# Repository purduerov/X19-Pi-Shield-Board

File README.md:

# Purdue ROV KiCad Board Template

Starter template for new PCB designs in Purdue ROV. Pre-configured with the team component library submodule, automatic Git clean filters, isolation rules, and CI/CD validation.

---

## 🚀 Quickstart: Opening the Project (Recommended)

**Always open the project using the 1-click launcher:**

* **Windows:** Double-click `LAUNCH_KICAD.bat`
* **macOS / Linux:** Run `./LAUNCH_KICAD.sh`

### What the Launcher Does Automatically:
1. ⚙️ **Configures Git Hooks & Clean Filters:** Sets up Git to strip volatile viewport/zoom coordinates on every commit, preventing merge conflicts.
2. 🔄 **Auto-Updates Component Library:** Pulls the freshest symbols, footprints, and 3D models from `purdue-rov-kicad-lib` before opening.
3. 📐 **Opens KiCad:** Launches the project file with all 6 central library categories pre-linked.

---

## Creating a New Board Repository

1. In GitHub, click **Use this template** > **Create a new repository**.
2. Name the repo to match the board function (e.g. `thruster-interface-board`).
3. Clone recursively so submodules are pulled:
   ```bash
   git clone --recursive https://github.com/purduerov/<your-repo-name>.git
   cd <your-repo-name>
   ```
   If cloned without `--recursive`, initialize the submodule:
   ```bash
   git submodule update --init --recursive
   ```

4. Prepare the board with `bootstrap.py` (renames starter files, writes the manifest, and installs the validation hook; `LAUNCH_KICAD` runs this automatically):
   ```bash
   python bootstrap.py --project-dir . --non-interactive
   ```

## Central Component Library & Manager GUI

The template is pre-configured with project-level library tables (`sym-lib-table` and `fp-lib-table`) pointing to `purdue-rov-kicad-lib`:
- `rov_passives`: Resistors, capacitors, inductors, crystals
- `rov_power`: Voltage regulators, buck/boost converters, MOSFETs, diodes
- `rov_logic`: MCUs, logic ICs, op-amps, level shifters, transceivers
- `rov_connectors`: Power terminals, XT60/XT30, headers, USB, JST connectors
- `rov_sensors`: IMUs, temperature, pressure sensors
- `rov_mech`: Mounting holes, standoffs, test points

### Launching the Library Manager GUI
To browse parts, inspect footprints, edit properties, or add/delete components in the shared library:
- **Windows:** Double-click `libs\purdue-rov-kicad-lib\LIBRARY_MANAGER.bat`
- **macOS / Linux:** Run `./libs/purdue-rov-kicad-lib/LIBRARY_MANAGER.sh`

## Design Rules & Clearances

- Clearance rules (JLCPCB 4-layer rules) are defined in `X19-Pi-Shield-Board.kicad_dru`.
- High-power thruster nets require a minimum 2.0 mm clearance from low-voltage logic (3.3V / 5V).

## Automated CI/CD & DevOps Preflight Checks

All CI/CD automation and tooling are centralized in [`purduerov/pcb-devops`](https://github.com/purduerov/pcb-devops):
1. **Automated Git Clean Filters:** Configured automatically by `.githooks/pre-commit` to prevent viewport/zoom merge noise.
2. **KiCad Symbol Linting:** Validates mandatory fields (`MPN`, `Manufacturer`, `Category`, `DigiKey`, `Datasheet`, `Temp_Range`) on all library components.
3. **ERC & DRC Validation:** Executes Electrical and Design Rules Checks via KiBot in GitHub Actions.
4. **Artifact Generation:** Automatically exports Schematic PDFs, Board Layout PDFs, and Interactive HTML BOMs on every pull request.

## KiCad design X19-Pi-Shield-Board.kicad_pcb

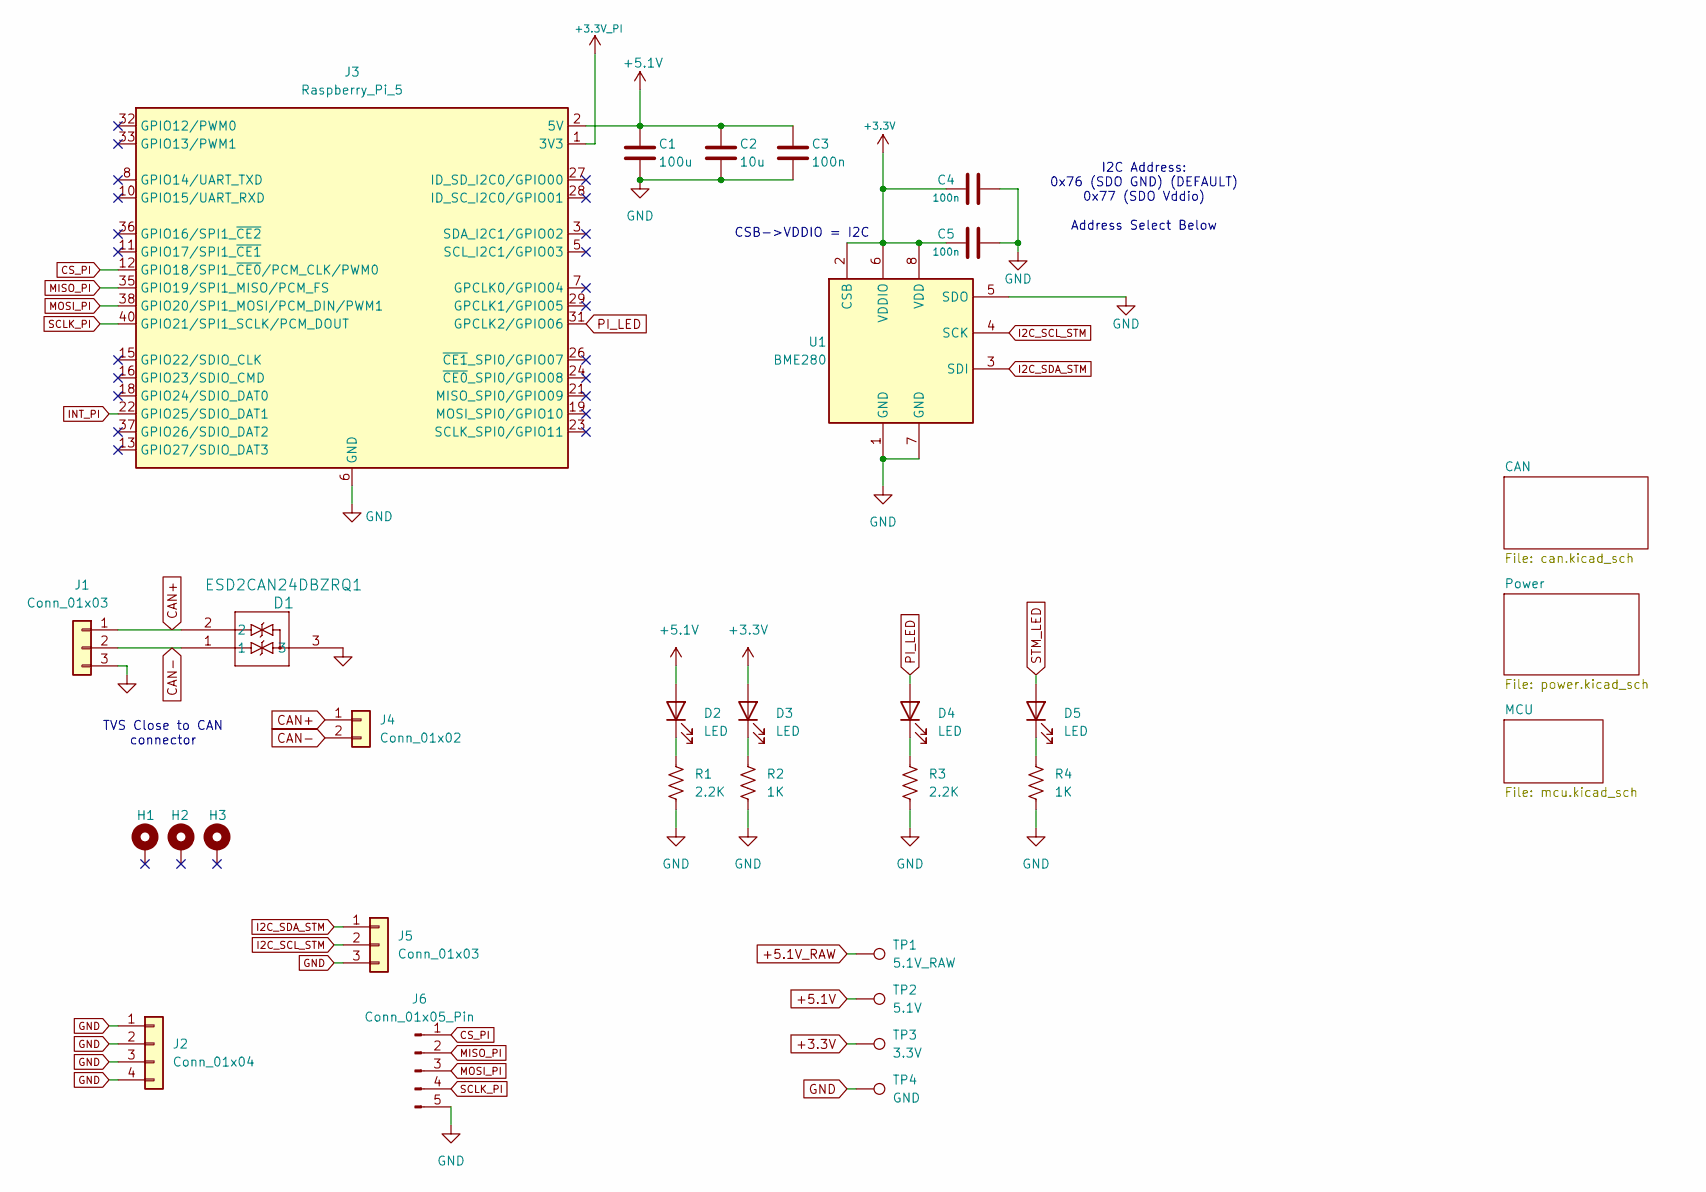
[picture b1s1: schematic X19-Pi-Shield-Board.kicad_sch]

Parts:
C1: 100u; CP_Elec_6.3x5.4; Part Number 865080343009
C2: 10u; C_0603_1608Metric_Pad1.08x0.95mm_HandSolder; Part Number CC0603MRX5R6BB106
C3, C4, C5: 100n; C_0603_1608Metric_Pad1.08x0.95mm_HandSolder; Part Number CC0603KRX7R8BB104
D1: ESD2CAN24DBZRQ1; SOT-23-3; Part Number ESD2CAN24DBZRQ1
D2, D3, D4, D5: LED; LED_0603_1608Metric_Pad1.05x0.95mm_HandSolder; Part Number LTST-C190GKT
H1, H2, H3: MountingHole_Pad; MountingHole_2.7mm_M2.5_Pad
J1: Conn_01x03; Molex_Micro-Fit_3.0_43650-0300_1x03_P3.00mm_Horizontal; Part Number 43650-0300
J2: Conn_01x04; PinHeader_1x04_P2.54mm_Vertical; Part Number Generic 2.54mm Pinheader
J3: Raspberry_Pi_5; PinSocket_2x20_P2.54mm_Vertical; Part Number 1528-1385-ND
J4: Conn_01x02; PinHeader_1x02_P2.54mm_Vertical; Part Number Generic 2.54mm Pinheader
J5: Conn_01x03; PinHeader_1x03_P2.54mm_Vertical; Part Number Generic 2.54mm Pinheader
J6: Conn_01x05_Pin; PinHeader_1x05_P2.54mm_Vertical; Part Number Generic 2.54mm Pinheader
R1, R3: 2.2K; R_0603_1608Metric_Pad0.98x0.95mm_HandSolder; Part Number RC0603FR-072K2L
R2, R4: 1K; R_0603_1608Metric_Pad0.98x0.95mm_HandSolder; Part Number RC0603FR-071KL
TP1: 5.1V_RAW; TestPoint_Pad_D1.0mm
TP2: 5.1V; TestPoint_Pad_D1.0mm
TP3: 3.3V; TestPoint_Pad_D1.0mm
TP4: GND; TestPoint_Pad_D1.0mm
U1: BME280; Bosch_LGA-8_2.5x2.5mm_P0.65mm_ClockwisePinNumbering; Part Number BME280

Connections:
+3.3V: C4.2, C5.1, D3.2 (A), TP3.1 (1_1), U1.2 (CSB), U1.6 (VDDIO), U1.8 (VDD); also elsewhere on the board
+3.3V_PI: J3.1 (3V3), J3.17 (3V3); also elsewhere on the board
+5.1V: C1.1, C2.1, C3.1, D2.2 (A), J3.2 (5V), J3.4 (5V), TP2.1 (1_1); also elsewhere on the board
+5.1V_RAW: TP1.1 (1_1); also elsewhere on the board
CAN+: D1.2, J1.1, J4.1; also elsewhere on the board
CAN-: D1.1, J1.2, J4.2; also elsewhere on the board
CS_PI: J3.12 (GPIO18/SPI1_~CE0/PCM_CLK/PWM0), J6.1; also elsewhere on the board
GND: C1.2, C2.2, C3.2, C4.1, C5.2, D1.3, J1.3, J2.1, J2.2, J2.3, J2.4, J3.6 (GND), J3.9 (GND), J3.14 (GND), J3.20 (GND), J3.25 (GND), J3.30 (GND), J3.34 (GND), J3.39 (GND), J5.3, J6.5, R1.2, R2.2, R3.2, R4.2, TP4.1 (1_1), U1.1 (GND), U1.5 (SDO), U1.7 (GND); also elsewhere on the board
I2C_SCL_STM: J5.2, U1.4 (SCK); also elsewhere on the board
I2C_SDA_STM: J5.1, U1.3 (SDI); also elsewhere on the board
INT_PI: J3.22 (GPIO25/SDIO_DAT1); also elsewhere on the board
MISO_PI: J3.35 (GPIO19/SPI1_MISO/PCM_FS), J6.2; also elsewhere on the board
MOSI_PI: J3.38 (GPIO20/SPI1_MOSI/PCM_DIN/PWM1), J6.3; also elsewhere on the board
unnamed: D2.1 (K), R1.1
unnamed: D3.1 (K), R2.1
unnamed: D4.1 (K), R3.1
unnamed: D5.1 (K), R4.1
PI_LED: D4.2 (A), J3.31 (GPCLK2/GPIO06)
SCLK_PI: J3.40 (GPIO21/SPI1_SCLK/PCM_DOUT), J6.4; also elsewhere on the board
STM_LED: D5.2 (A); also elsewhere on the board

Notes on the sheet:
CSB->VDDIO = I2C
TVS Close to CAN connector
I2C Address: 0x76 (SDO GND) (DEFAULT) 0x77 (SDO Vddio) Address Select Below

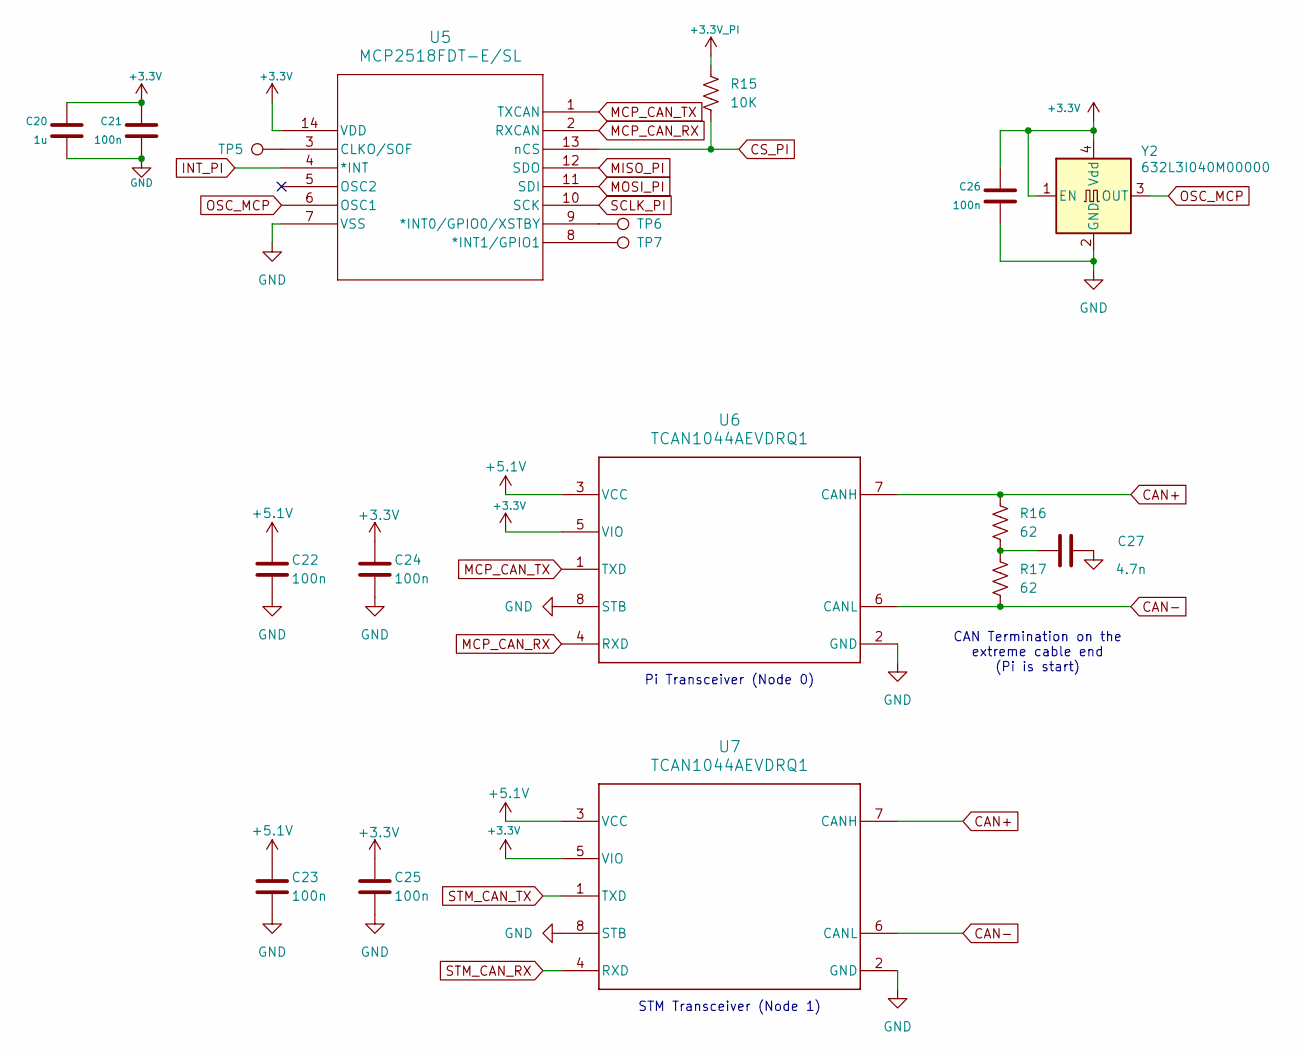
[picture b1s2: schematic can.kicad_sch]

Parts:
C20: 1u; C_0603_1608Metric_Pad1.08x0.95mm_HandSolder; Part Number CC0603KRX5R6BB105
C21, C22, C23, C24, C25, C26: 100n; C_0603_1608Metric_Pad1.08x0.95mm_HandSolder; Part Number CC0603KRX7R8BB104
C27: 4.7n; C_0603_1608Metric_Pad1.08x0.95mm_HandSolder; Part Number CC0603KRX7R9BB472
R15: 10K; R_0603_1608Metric_Pad0.98x0.95mm_HandSolder; Part Number RC0603FR-0710KL
R16, R17: 62; R_0603_1608Metric_Pad0.98x0.95mm_HandSolder; Part Number RC0603FR-0762RL
TP5: SOF1; TestPoint_Pad_D1.0mm
TP6: INT0; TestPoint_Pad_D1.0mm
TP7: INT1; TestPoint_Pad_D1.0mm
U5: MCP2518FDT-E/SL; SOIC-14_3.9x8.7mm_P1.27mm; Part Number MCP2518FDT-E/SL
U6, U7: TCAN1044AEVDRQ1; SOIC-8_3.9x4.9mm_P1.27mm; Part Number TCAN1044AEVDRQ1
Y2: 632L3I040M00000; Crystal_SMD_3225-4Pin_3.2x2.5mm; Part Number 632L3I040M00000

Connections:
+3.3V: C20.1, C21.1, C24.1, C25.1, C26.1, U5.14 (VDD), U6.5 (VIO), U7.5 (VIO), Y2.1 (EN), Y2.4 (Vdd); also elsewhere on the board
+3.3V_PI: R15.1; also elsewhere on the board
+5.1V: C22.1, C23.1, U6.3 (VCC), U7.3 (VCC); also elsewhere on the board
CAN+: R16.1, U6.7 (CANH), U7.7 (CANH); also elsewhere on the board
CAN-: R17.2, U6.6 (CANL), U7.6 (CANL); also elsewhere on the board
CS_PI: R15.2, U5.13 (nCS); also elsewhere on the board
GND: C20.2, C21.2, C22.2, C23.2, C24.2, C25.2, C26.2, C27.2, U5.7 (VSS), U6.2 (GND), U6.8 (STB), U7.2 (GND), U7.8 (STB), Y2.2 (GND); also elsewhere on the board
INT_PI: U5.4 (*INT); also elsewhere on the board
MCP_CAN_RX: U5.2 (RXCAN), U6.4 (RXD)
MCP_CAN_TX: U5.1 (TXCAN), U6.1 (TXD)
MISO_PI: U5.12 (SDO); also elsewhere on the board
MOSI_PI: U5.11 (SDI); also elsewhere on the board
unnamed: C27.1, R16.2, R17.1
unnamed: TP6.1 (1_1), U5.9 (*INT0/GPIO0/XSTBY)
unnamed: TP7.1 (1_1), U5.8 (*INT1/GPIO1)
unnamed: TP5.1 (1_1), U5.3 (CLKO/SOF)
OSC_MCP: U5.6 (OSC1), Y2.3 (OUT)
SCLK_PI: U5.10 (SCK); also elsewhere on the board
STM_CAN_RX: U7.4 (RXD); also elsewhere on the board
STM_CAN_TX: U7.1 (TXD); also elsewhere on the board

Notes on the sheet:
CAN Termination on the extreme cable end (Pi is start)
Pi Transceiver (Node 0)
STM Transceiver (Node 1)

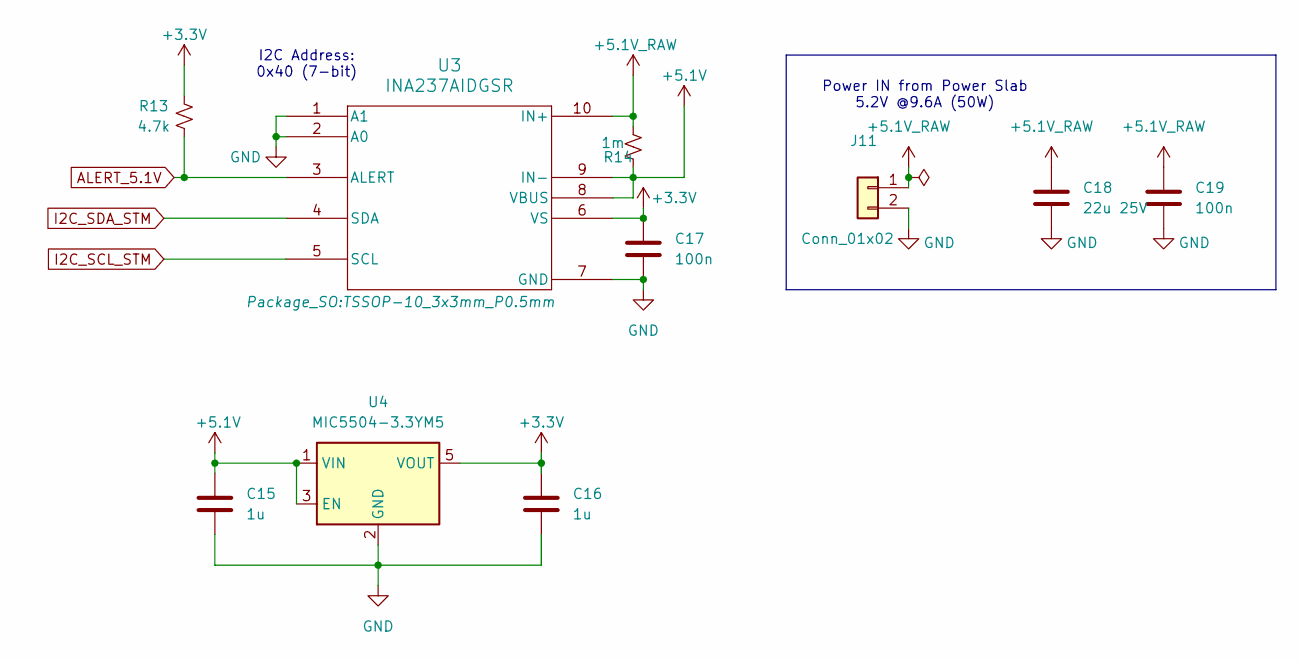
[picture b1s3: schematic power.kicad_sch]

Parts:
C15, C16: 1u; C_0603_1608Metric_Pad1.08x0.95mm_HandSolder; Part Number CC0603KRX5R6BB105
C17, C19: 100n; C_0603_1608Metric_Pad1.08x0.95mm_HandSolder; Part Number CC0603KRX7R8BB104
C18: 22u 25V; C_1206_3216Metric_Pad1.33x1.80mm_HandSolder; Part Number CC1206KKX5R8BB226
J11: Conn_01x02; Molex_Micro-Fit_3.0_43650-0200_1x02_P3.00mm_Horizontal; Part Number 43650-0200
R13: 4.7k; R_0603_1608Metric_Pad0.98x0.95mm_HandSolder; Part Number RC0603FR-074K7L
R14: 1m; R_1206_3216Metric_Pad1.30x1.75mm_HandSolder; Part Number PCS1206FR0010ET
U3: INA237AIDGSR; TSSOP-10_3x3mm_P0.5mm; Part Number INA237AIDGSR
U4: MIC5504-3.3YM5; SOT-23-5; Part Number MIC5504-3.3YM5-TR

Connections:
+3.3V: C16.1, C17.1, R13.2, U3.6 (VS), U4.5 (VOUT); also elsewhere on the board
+5.1V: C15.1, R14.1, U3.8 (VBUS), U3.9 (IN-), U4.1 (VIN), U4.3 (EN); also elsewhere on the board
+5.1V_RAW: C18.1, C19.1, J11.1, R14.2, U3.10 (IN+); also elsewhere on the board
ALERT_5.1V: R13.1, U3.3 (ALERT); also elsewhere on the board
GND: C15.2, C16.2, C17.2, C18.2, C19.2, J11.2, U3.1 (A1), U3.2 (A0), U3.7 (GND), U4.2 (GND); also elsewhere on the board
I2C_SCL_STM: U3.5 (SCL); also elsewhere on the board
I2C_SDA_STM: U3.4 (SDA); also elsewhere on the board

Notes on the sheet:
I2C Address: 0x40 (7-bit)
Power IN from Power Slab 5.2V @9.6A (50W)

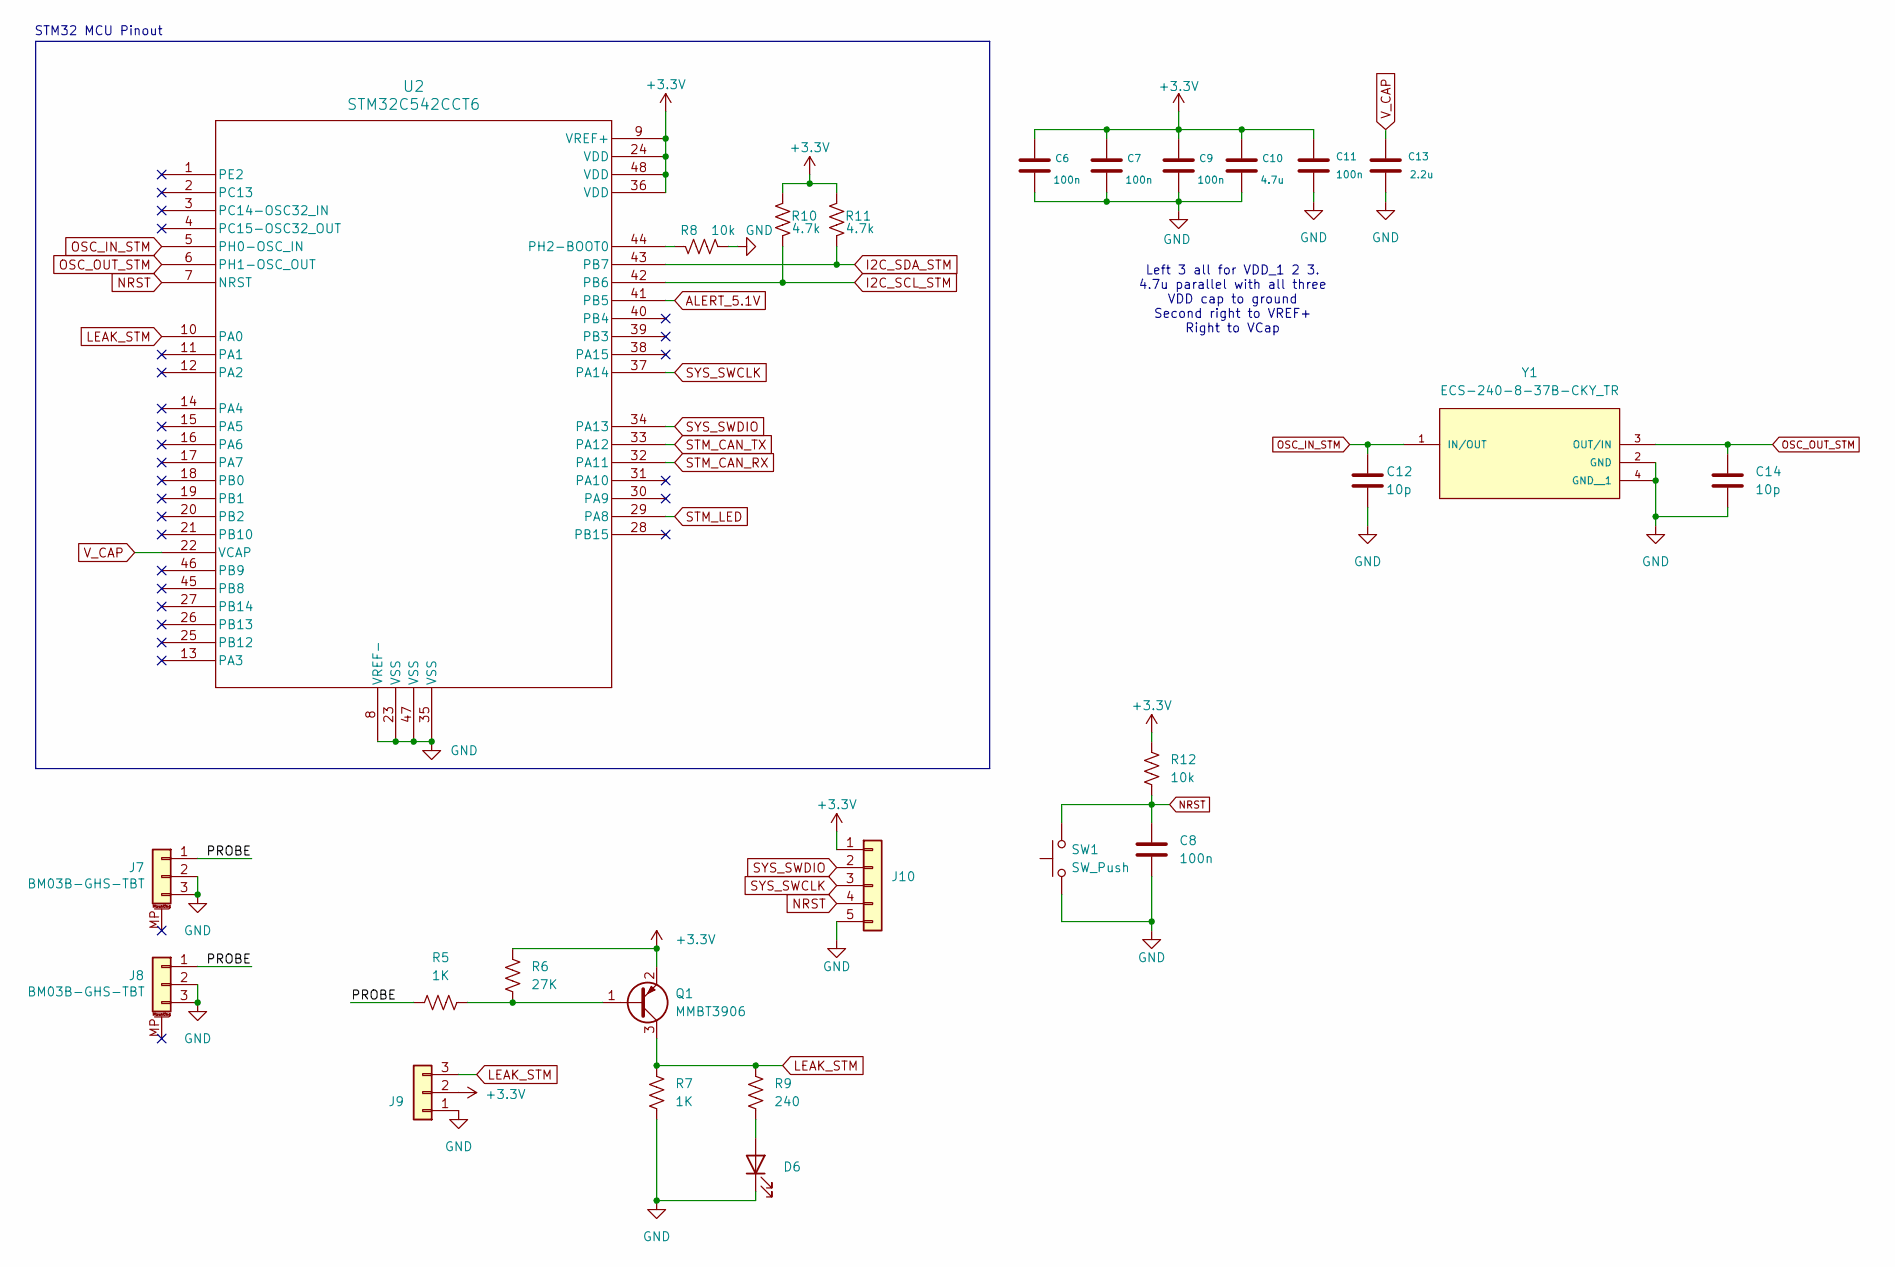
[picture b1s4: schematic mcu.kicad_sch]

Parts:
C6, C7, C8, C9, C11: 100n; C_0603_1608Metric_Pad1.08x0.95mm_HandSolder; Part Number CC0603KRX7R8BB104
C10: 4.7u; C_0603_1608Metric_Pad1.08x0.95mm_HandSolder; Part Number CC0603KRX5R6BB475
C12, C14: 10p; C_0603_1608Metric_Pad1.08x0.95mm_HandSolder; Part Number CC0603JRNPO9BN100
C13: 2.2u; C_0603_1608Metric_Pad1.08x0.95mm_HandSolder; Part Number CC0603KRX5R6BB225
D6: LED; LED_0603_1608Metric_Pad1.05x0.95mm_HandSolder; Part Number LTST-C190GKT
J7, J8: BM03B-GHS-TBT; JST_GH_BM03B-GHS-TBT_1x03-1MP_P1.25mm_Vertical; Part Number BM03B-GHS-TBT
J9: Conn_01x03; PinHeader_1x03_P2.54mm_Vertical; Part Number Generic 2.54mm Pinheader
J10: Conn_01x05; PinHeader_1x05_P2.54mm_Vertical; Part Number Generic 2.54mm Pinheader
Q1: MMBT3906; SOT-23; Part Number MMBT3906
R5, R7: 1K; R_0603_1608Metric_Pad0.98x0.95mm_HandSolder; Part Number RC0603FR-071KL
R6: 27K; R_0603_1608Metric_Pad0.98x0.95mm_HandSolder; Part Number RC0603FR-0727KL
R8, R12: 10k; R_0603_1608Metric_Pad0.98x0.95mm_HandSolder; Part Number RC0603FR-0710KL
R9: 240; R_0603_1608Metric_Pad0.98x0.95mm_HandSolder; Part Number RC0603FR-07240RL
R10, R11: 4.7k; R_0603_1608Metric_Pad0.98x0.95mm_HandSolder; Part Number RC0603FR-074K7L
SW1: SW_Push; SW_SPST_B3U-1000P; Part Number B3U-1000P
U2: STM32C542CCT6; LQFP-48_7x7mm_P0.5mm; Part Number STM32C542CCT6
Y1: ECS-240-8-37B-CKY_TR; Crystal_SMD_2016-4Pin_2.0x1.6mm; Part Number ECS-240-8-37B-CKY-TR

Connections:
+3.3V: C6.1, C7.1, C9.1, C10.1, C11.1, J9.2, J10.1, Q1.2 (E), R6.1, R10.2, R11.2, R12.1, U2.9 (VREF+), U2.24 (VDD), U2.36 (VDD), U2.48 (VDD); also elsewhere on the board
/MCU/PROBE: J7.1, J8.1, R5.1
ALERT_5.1V: U2.41 (PB5); also elsewhere on the board
GND: C6.2, C7.2, C8.2, C9.2, C10.2, C11.2, C12.1, C13.2, C14.2, D6.1 (K), J7.2, J7.3, J8.2, J8.3, J9.1, J10.5, R7.2, R8.1, SW1.1, U2.8 (VREF-), U2.23 (VSS), U2.35 (VSS), U2.47 (VSS), Y1.2 (GND), Y1.4 (GND__1); also elsewhere on the board
I2C_SCL_STM: R10.1, U2.42 (PB6); also elsewhere on the board
I2C_SDA_STM: R11.1, U2.43 (PB7); also elsewhere on the board
LEAK_STM: J9.3, Q1.3 (C), R7.1, R9.1, U2.10 (PA0)
NRST: C8.1, J10.4, R12.2, SW1.2, U2.7 (NRST)
unnamed: D6.2 (A), R9.2
unnamed: Q1.1 (B), R5.2, R6.2
unnamed: R8.2, U2.44 (PH2-BOOT0)
OSC_IN_STM: C12.2, U2.5 (PH0-OSC_IN), Y1.1 (IN/OUT)
OSC_OUT_STM: C14.1, U2.6 (PH1-OSC_OUT), Y1.3 (OUT/IN)
STM_CAN_RX: U2.32 (PA11); also elsewhere on the board
STM_CAN_TX: U2.33 (PA12); also elsewhere on the board
STM_LED: U2.29 (PA8); also elsewhere on the board
SYS_SWCLK: J10.3, U2.37 (PA14)
SYS_SWDIO: J10.2, U2.34 (PA13)
V_CAP: C13.1, U2.22 (VCAP)

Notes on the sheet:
STM32 MCU Pinout
Left 3 all for VDD_1 2 3. 4.7u parallel with all three VDD cap to ground Second right to VREF+ Right to VCap

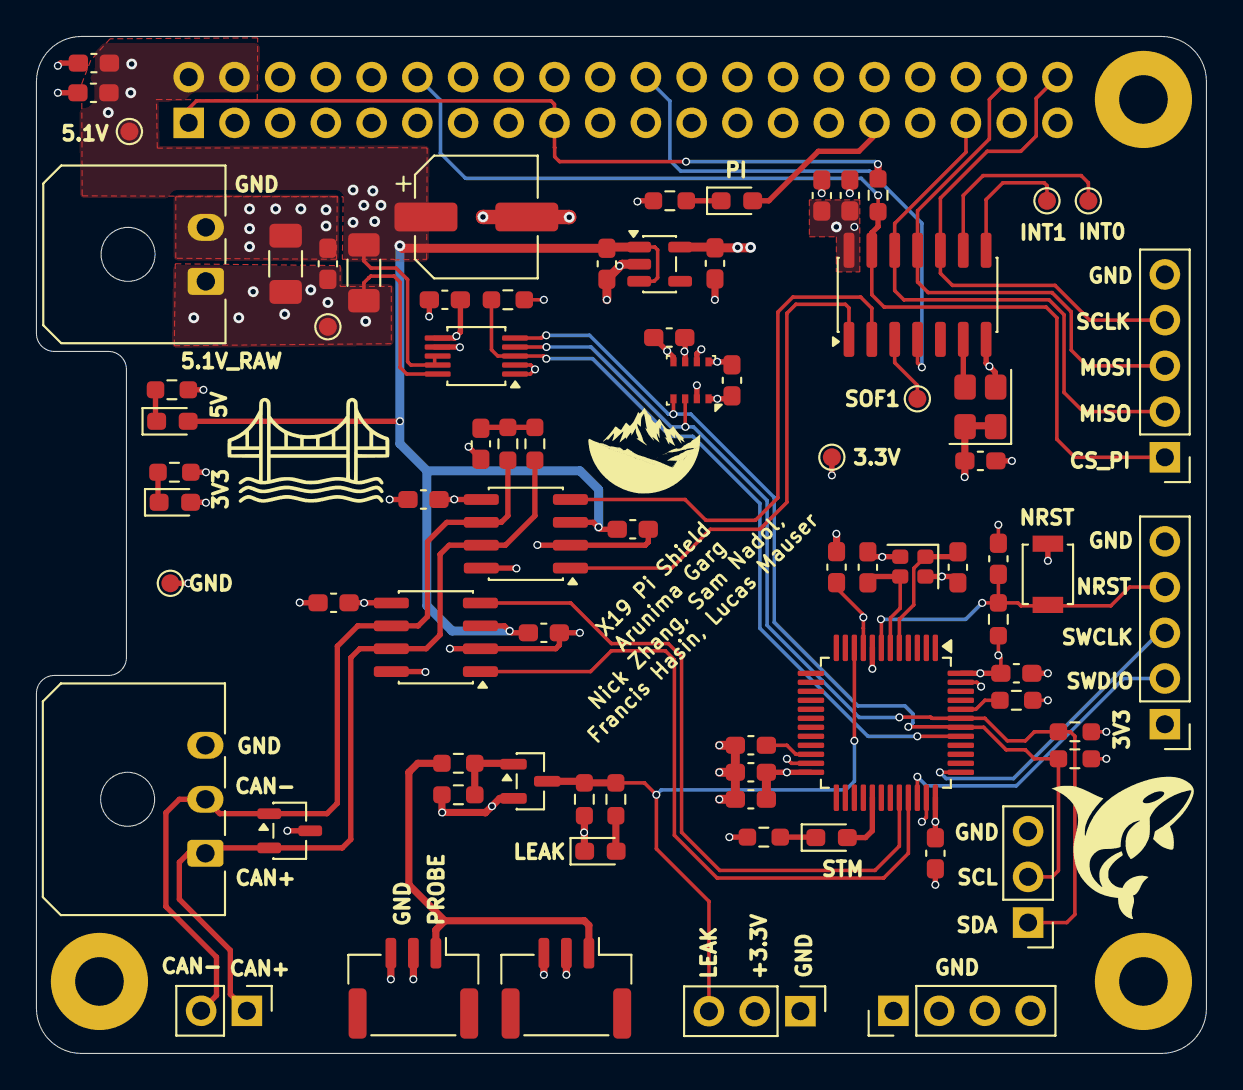
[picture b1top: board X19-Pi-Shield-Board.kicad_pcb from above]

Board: 4 copper layers, 65.0 x 56.5 mm, 82 parts (1 on the bottom side), 41 nets.

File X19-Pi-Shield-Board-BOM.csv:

Row,Description,Part,References,Value,Footprint,Quantity Per PCB,Status,Datasheet,digikey,Part Number,Sim.Pins,MF,PACKAGE,PRICE,STANDARD,MP,AVAILABILITY,Sim.Device
1,Unpolarized capacitor,C,C12 C14,10p,C_0603_1608Metric_Pad1.08x0.95mm_HandSolder,2, ,,,CC0603JRNPO9BN100,,,,,,,,
2,Unpolarized capacitor,C,C27,4.7n,C_0603_1608Metric_Pad1.08x0.95mm_HandSolder,1, ,,,CC0603KRX7R9BB472,,,,,,,,
3,Unpolarized capacitor,C,C3 C4 C5 C6 C7 C8 C9 C11 C17 C19 C21 C22 C23 C24 C25 C26,100n,C_0603_1608Metric_Pad1.08x0.95mm_HandSolder,16, ,,,CC0603KRX7R8BB104,,,,,,,,
4,Unpolarized capacitor,C,C15 C16 C20,1u,C_0603_1608Metric_Pad1.08x0.95mm_HandSolder,3, ,,,CC0603KRX5R6BB105,,,,,,,,
5,Unpolarized capacitor,C,C13,2.2u,C_0603_1608Metric_Pad1.08x0.95mm_HandSolder,1, ,,,CC0603KRX5R6BB225,,,,,,,,
6,Unpolarized capacitor,C,C10,4.7u,C_0603_1608Metric_Pad1.08x0.95mm_HandSolder,1, ,,,CC0603KRX5R6BB475,,,,,,,,
7,Unpolarized capacitor,C,C2,10u,C_0603_1608Metric_Pad1.08x0.95mm_HandSolder,1, ,,,CC0603MRX5R6BB106,,,,,,,,
8,Unpolarized capacitor,C,C18,22u 25V,C_1206_3216Metric_Pad1.33x1.80mm_HandSolder,1, ,,,CC1206KKX5R8BB226,,,,,,,,
9,Unpolarized capacitor,C,C1,100u,CP_Elec_6.3x5.4,1, ,,,865080343009,,,,,,,,
10,,ESD2CAN24DBZRQ1,D1,ESD2CAN24DBZRQ1,SOT-23-3,1, ,ESD2CAN24DBZRQ1,,ESD2CAN24DBZRQ1,,,,,,,,
11,Light emitting diode,LED,D2 D3 D4 D5 D6,LED,LED_0603_1608Metric_Pad1.05x0.95mm_HandSolder,5, ,,,LTST-C190GKT,1=K 2=A,,,,,,,
12,"Generic connectable mounting pin connector, single row, 01x03, script generated (kicad-library-utils/schlib/autogen/connector/)",Conn_01x03_MountingPin,J7 J8,BM03B-GHS-TBT,JST_GH_BM03B-GHS-TBT_1x03-1MP_P1.25mm_Vertical,2, ,,,BM03B-GHS-TBT,,,,,,,,
13,"Generic connector, single row, 01x02, script generated (kicad-library-utils/schlib/autogen/connector/)",Conn_01x02,J11,Conn_01x02,Molex_Micro-Fit_3.0_43650-0200_1x02_P3.00mm_Horizontal,1, ,,,43650-0200,,,,,,,,
14,"Generic connector, single row, 01x03, script generated (kicad-library-utils/schlib/autogen/connector/)",Conn_01x03,J1,Conn_01x03,Molex_Micro-Fit_3.0_43650-0300_1x03_P3.00mm_Horizontal,1, ,,,43650-0300,,,,,,,,
15,Raspberry Pi 4 Model B,Raspberry_Pi_4,J3,Raspberry_Pi_5,PinSocket_2x20_P2.54mm_Vertical,1, ,https://datasheets.raspberrypi.com/rpi4/raspberry-pi-4-datas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,,1528-1385-ND,,,,,,,,
16,"-0.2A Ic, -40V Vce, Small Signal PNP Transistor, SOT-23",MMBT3906,Q1,MMBT3906,SOT-23,1, ,https://www.onsemi.com/pdf/datasheet/pzt3906-d.pdf,,MMBT3906,1=B 2=E 3=C,,,,,,,PNP
17,"Resistor, small US symbol",R_Small_US,R14,1m,PCS1206FR0010ET,1, ,Resistor_SMD:R_1206_3216Metric_Pad1.30x1.75mm_HandSolder,,,,,,,,,,
18,"Resistor, US symbol",R_US,R16 R17,62,R_0603_1608Metric_Pad0.98x0.95mm_HandSolder,2, ,,,RC0603FR-0762RL,,,,,,,,
19,"Resistor, US symbol",R_US,R9,240,R_0603_1608Metric_Pad0.98x0.95mm_HandSolder,1, ,,,RC0603FR-07240RL,,,,,,,,
20,"Resistor, US symbol",R_US,R2 R4 R5 R7,1K,R_0603_1608Metric_Pad0.98x0.95mm_HandSolder,4, ,,,RC0603FR-071KL,,,,,,,,
21,"Resistor, US symbol",R_US,R1 R3,2.2K,R_0603_1608Metric_Pad0.98x0.95mm_HandSolder,2, ,,,RC0603FR-072K2L,,,,,,,,
22,"Resistor, US symbol",R_US,R10 R11,4.7k,R_0603_1608Metric_Pad0.98x0.95mm_HandSolder,2, ,,,RC0603FR-074K7L,,,,,,,,
23,"Resistor, small US symbol",R_Small_US,R13,4.7k,R_0603_1608Metric_Pad0.98x0.95mm_HandSolder,1, ,,,RC0603FR-074K7L,,,,,,,,
24,"Resistor, US symbol",R_US,R8 R12 R15,10k,R_0603_1608Metric_Pad0.98x0.95mm_HandSolder,3, ,,,RC0603FR-0710KL,,,,,,,,
25,"Resistor, US symbol",R_US,R6,27K,R_0603_1608Metric_Pad0.98x0.95mm_HandSolder,1, ,,,RC0603FR-0727KL,,,,,,,,
26,"Push button switch, generic, two pins",SW_Push,SW1,SW_Push,SW_SPST_B3U-1000P,1, ,,,B3U-1000P,,,,,,,,
27,"3-in-1 sensor, humidity, pressure, temperature, I2C and SPI interface, 1.71-3.6V, LGA-8",BME280,U1,BME280,Bosch_LGA-8_2.5x2.5mm_P0.65mm_ClockwisePinNumbering,1, ,https://www.bosch-sensortec.com/media/boschsensortec/downloa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,,BME280,,,,,,,,
28,,INA237AIDGSR,U3,INA237AIDGSR,TSSOP-10_3x3mm_P0.5mm,1, ,https://www.ti.com/lit/gpn/ina237,,INA237AIDGSR,,,,,,,,
29,,MCP2518FDT-E_QBB,U5,MCP2518FDT-E/SL,SOIC-14_3.9x8.7mm_P1.27mm,1, ,MCP2518FDT-E/SL,,MCP2518FDT-E/SL,,,,,,,,
30,"300mA Low-dropout Voltage Regulator, Vout 3.3V, Vin up to 5.5V, SOT-23",MIC5504-3.3YM5,U4,MIC5504-3.3YM5,SOT-23-5,1, ,http://ww1.microchip.com/downloads/en/DeviceDoc/MIC550X.pdf,,MIC5504-3.3YM5-TR,,,,,,,,
31,,STM32C542CCT6,U2,STM32C542CCT6,LQFP-48_7x7mm_P0.5mm,1, ,https://www.st.com/resource/en/datasheet/stm32c542cc.pdf,,STM32C542CCT6,,,,,,,,
32,,TCAN1044VDRQ1,U6 U7,TCAN1044AEVDRQ1,SOIC-8_3.9x4.9mm_P1.27mm,2, ,https://www.ti.com/lit/ds/symlink/tcan1044aev-q1.pdf,,TCAN1044AEVDRQ1,,,,,,,,
33,"3.3V CMOS SMD Crystal Clock Oscillator, Abracon",ASE-xxxMHz,Y2,632L3I040M00000,Crystal_SMD_3225-4Pin_3.2x2.5mm,1, ,http://www.abracon.com/Oscillators/ASV.pdf,,632L3I040M00000,,,,,,,,
34,The sub miniature ECX-32 is a compact SMD Crystal.,ECS-120-18-33-JGN-TR,Y1,ECS-240-8-37B-CKY_TR,Crystal_SMD_2016-4Pin_2.0x1.6mm,1, ,,,ECS-240-8-37B-CKY-TR,,ECS INC,SMD-4 ECX,,Manufacturer recommendations,ECX-32,Good,





Project info:
Schematic:,X19-Pi-Shield-Board
Variant:,default
Revision:,
Date:,2026-11-19_22-14-04
KiCad Version:,10.0.5-unknown-202607221313~667fa36054~ubuntu25.10.1
Statistics:
Component Groups:,34
Component Count:,66
Fitted Components:,66
Number of PCBs:,1
Total Components:,66
